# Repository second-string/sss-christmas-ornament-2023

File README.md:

# Berghain PCB Christmas Ornament
Designed by Second String Studios

## Boards

## Layout

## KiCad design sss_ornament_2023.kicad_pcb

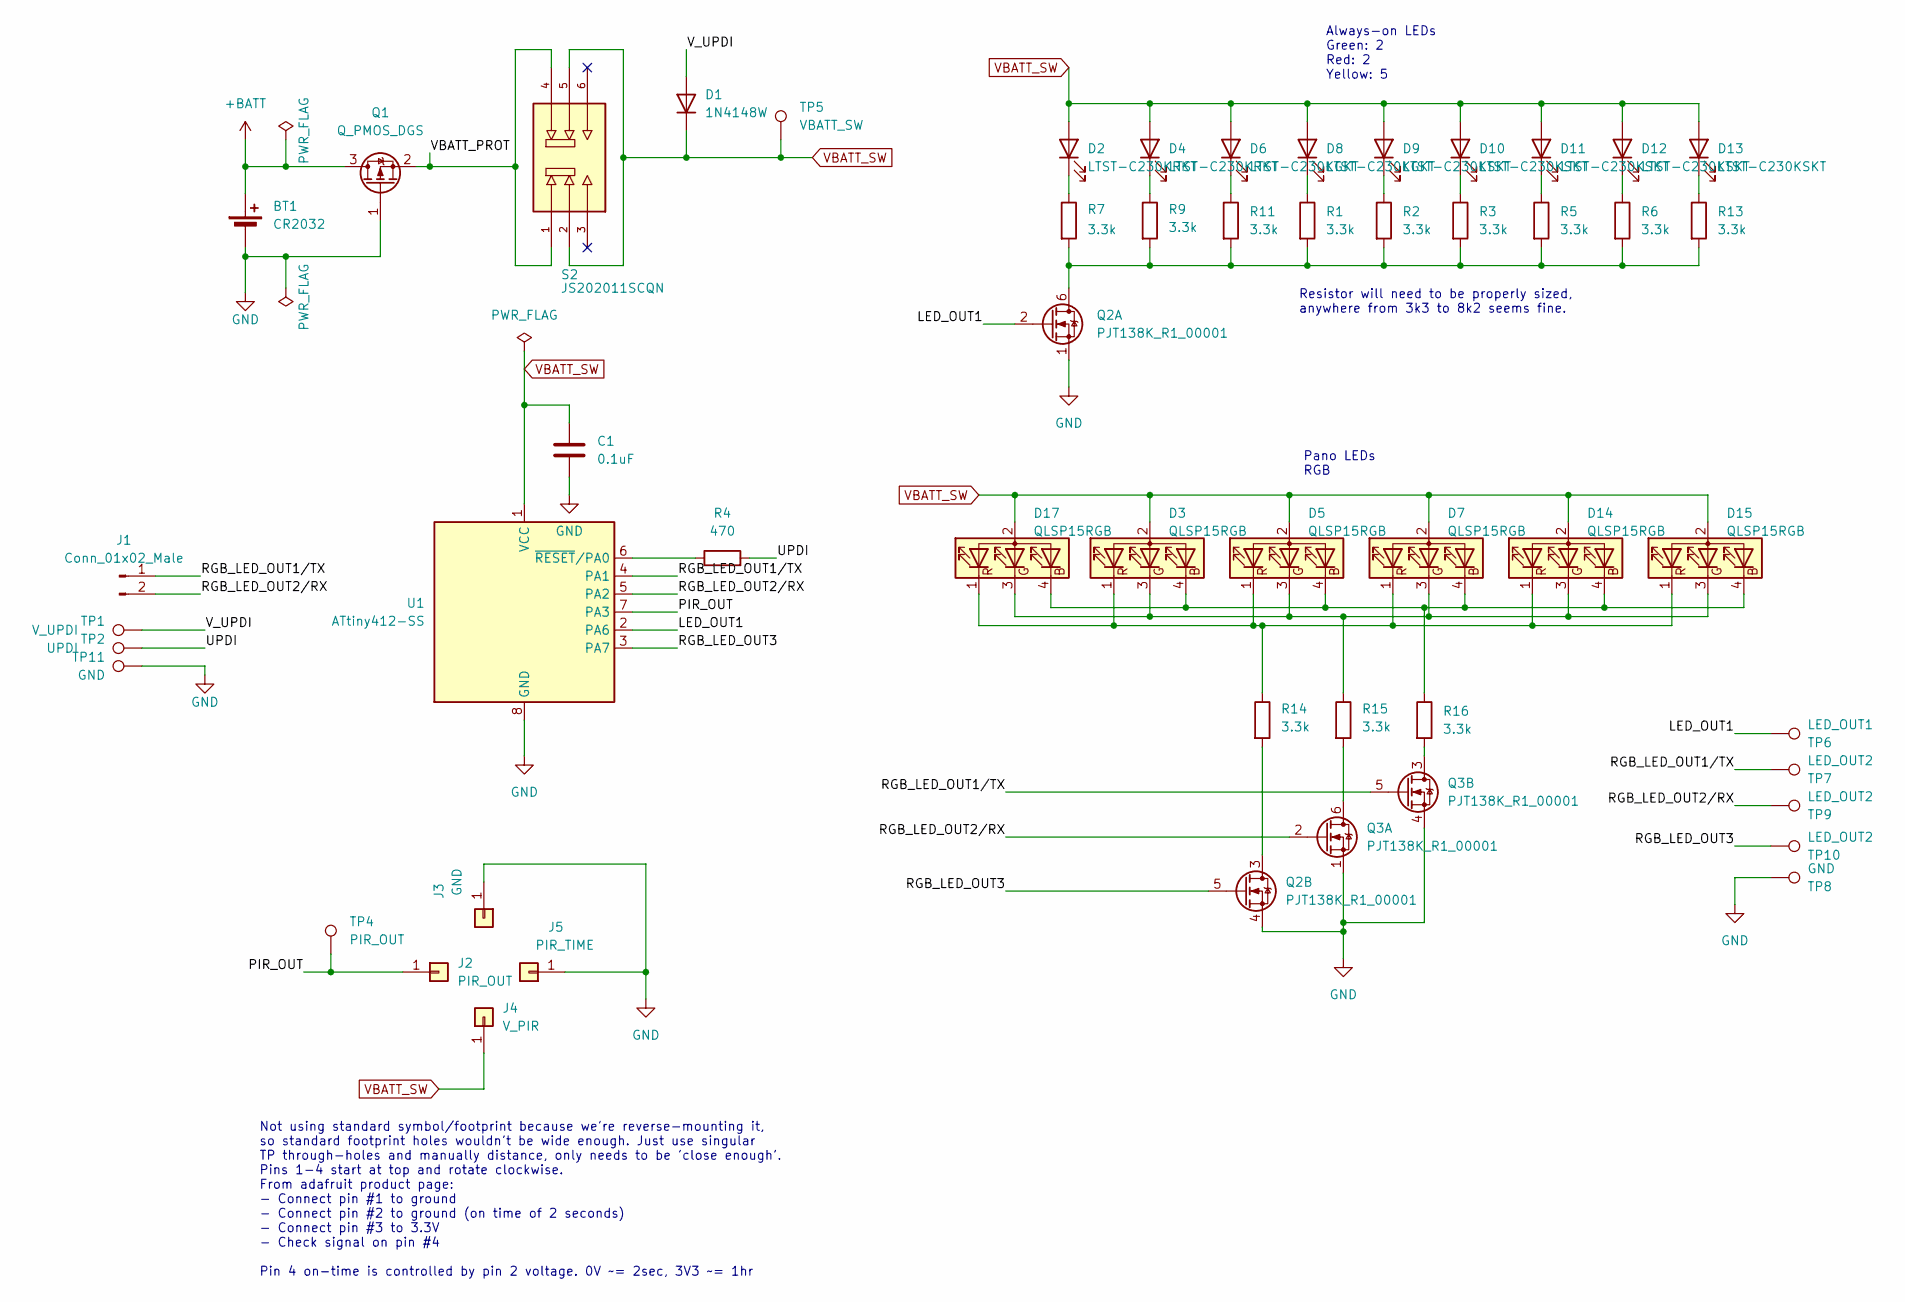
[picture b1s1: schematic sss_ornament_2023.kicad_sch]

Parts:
BT1: CR2032; BatteryHolder_Keystone_3002_1x2032
C1: 0.1uF; C_0805_2012Metric_Pad1.18x1.45mm_HandSolder
D1: 1N4148W; D_SOD-123
D2, D4: LTST-C230KRKT; LED_LTST-C230K
D3, D5, D7, D14, D15, D17: QLSP15RGB
D6, D8: LTST-C230KGKT; LED_LTST-C230K
D9, D10, D11, D12, D13: LTST-C230KSKT; LED_LTST-C230K
J1: Conn_01x02_Male; Harwin_M20-89003xx_1x02_P2.54mm_Horizontal
J2: PIR_OUT; PinHeader_1x01_P2.54mm_Vertical
J3: GND; PinHeader_1x01_P2.54mm_Vertical
J4: V_PIR; PinHeader_1x01_P2.54mm_Vertical
J5: PIR_TIME; PinHeader_1x01_P2.54mm_Vertical
Q1: Q_PMOS_DGS; SOT-723
Q2, Q3: PJT138K_R1_00001; SOT-363_SC-70-6_Handsoldering
R1, R2, R3, R5, R6, R7, R9, R11, R13, R14, R15, R16: 3.3k; R_0805_2012Metric_Pad1.20x1.40mm_HandSolder
R4: 470; R_0805_2012Metric_Pad1.20x1.40mm_HandSolder
S2: JS202011SCQN; SW_JS202011SCQN
TP1: V_UPDI; TestPoint_Pad_D2.0mm
TP2: UPDI; TestPoint_Pad_D2.0mm
TP4: PIR_OUT; TestPoint_Pad_D2.0mm
TP5: VBATT_SW; TestPoint_Pad_D2.0mm
TP6: LED_OUT1; TestPoint_Pad_D2.0mm
TP7, TP9, TP10: LED_OUT2; TestPoint_Pad_D2.0mm
TP8, TP11: GND; TestPoint_Pad_D2.0mm
U1: ATtiny412-SS; SOIC-8_3.9x4.9mm_P1.27mm

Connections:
+BATT: BT1.1 (+), Q1.3 (D)
/LED_OUT1: Q2.2 (G), TP6.1, U1.2 (PA6)
/PIR_OUT: J2.1, TP4.1, U1.7 (PA3)
/RGB_LED_OUT1/TX: J1.1, Q3.5 (G), TP7.1, U1.4 (PA1)
/RGB_LED_OUT2/RX: J1.2, Q3.2 (G), TP9.1, U1.5 (PA2)
/RGB_LED_OUT3: Q2.5 (G), TP10.1, U1.3 (PA7)
/UPDI: R4.2, TP2.1
/VBATT_PROT: Q1.2 (S), S2.1, S2.4
/V_UPDI: D1.2 (A), TP1.1
GND: BT1.2 (-), C1.2, J3.1, J5.1, Q1.1 (G), Q2.1 (S), Q2.4 (S), Q3.1 (S), Q3.4 (S), TP8.1, TP11.1, U1.8 (GND)
unnamed: D2.1 (K), R7.1
unnamed: D4.1 (K), R9.1
unnamed: D6.1 (K), R11.1
unnamed: D8.1 (K), R1.1
unnamed: D9.1 (K), R2.1
unnamed: D10.1 (K), R3.1
unnamed: D11.1 (K), R5.1
unnamed: D12.1 (K), R6.1
unnamed: D13.1 (K), R13.1
unnamed: D3.4 (BK), D5.4 (BK), D7.4 (BK), D14.4 (BK), D15.4 (BK), D17.4 (BK), R16.1
unnamed: D3.3 (GK), D5.3 (GK), D7.3 (GK), D14.3 (GK), D15.3 (GK), D17.3 (GK), R15.1
unnamed: D3.1 (RK), D5.1 (RK), D7.1 (RK), D14.1 (RK), D15.1 (RK), D17.1 (RK), R14.1
unnamed: Q2.6 (D), R1.2, R2.2, R3.2, R5.2, R6.2, R7.2, R9.2, R11.2, R13.2
unnamed: Q2.3 (D), R14.2
unnamed: Q3.6 (D), R15.2
unnamed: Q3.3 (D), R16.2
unnamed: R4.1, U1.6 (~RESET/PA0)
VBATT_SW: C1.1, D1.1 (K), D2.2 (A), D3.2 (A), D4.2 (A), D5.2 (A), D6.2 (A), D7.2 (A), D8.2 (A), D9.2 (A), D10.2 (A), D11.2 (A), D12.2 (A), D13.2 (A), D14.2 (A), D15.2 (A), D17.2 (A), J4.1, S2.2, S2.5, TP5.1, U1.1 (VCC)

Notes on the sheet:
Resistor will need to be properly sized, anywhere from 3k3 to 8k2 seems fine.
Pano LEDs RGB
Not using standard symbol/footprint because we're reverse-mounting it, so standard footprint holes wouldn't be wide enough. Just use singular TP through-holes and manually distance, only needs to be 'close enough'. Pins 1-4 start at top and rotate clockwise. From adafruit product page: - Connect pi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
Always-on LEDs Green: 2 Red: 2 Yellow: 5

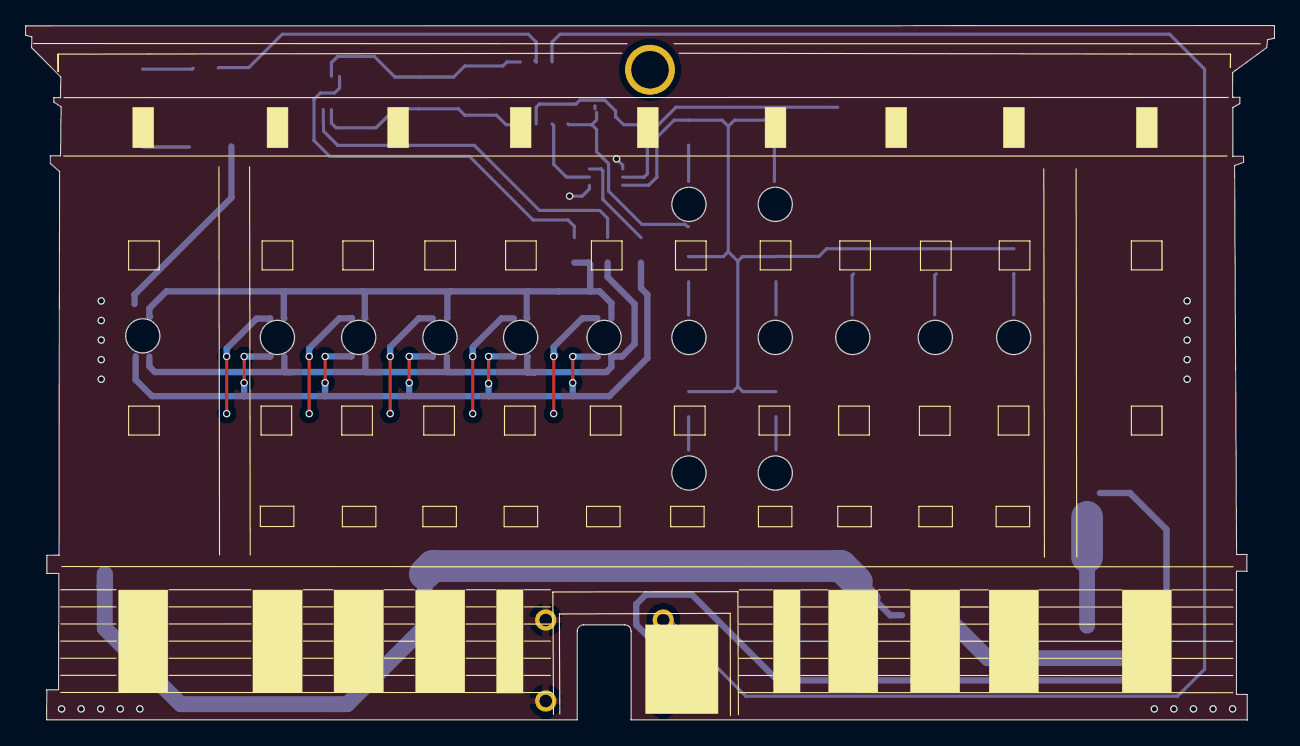
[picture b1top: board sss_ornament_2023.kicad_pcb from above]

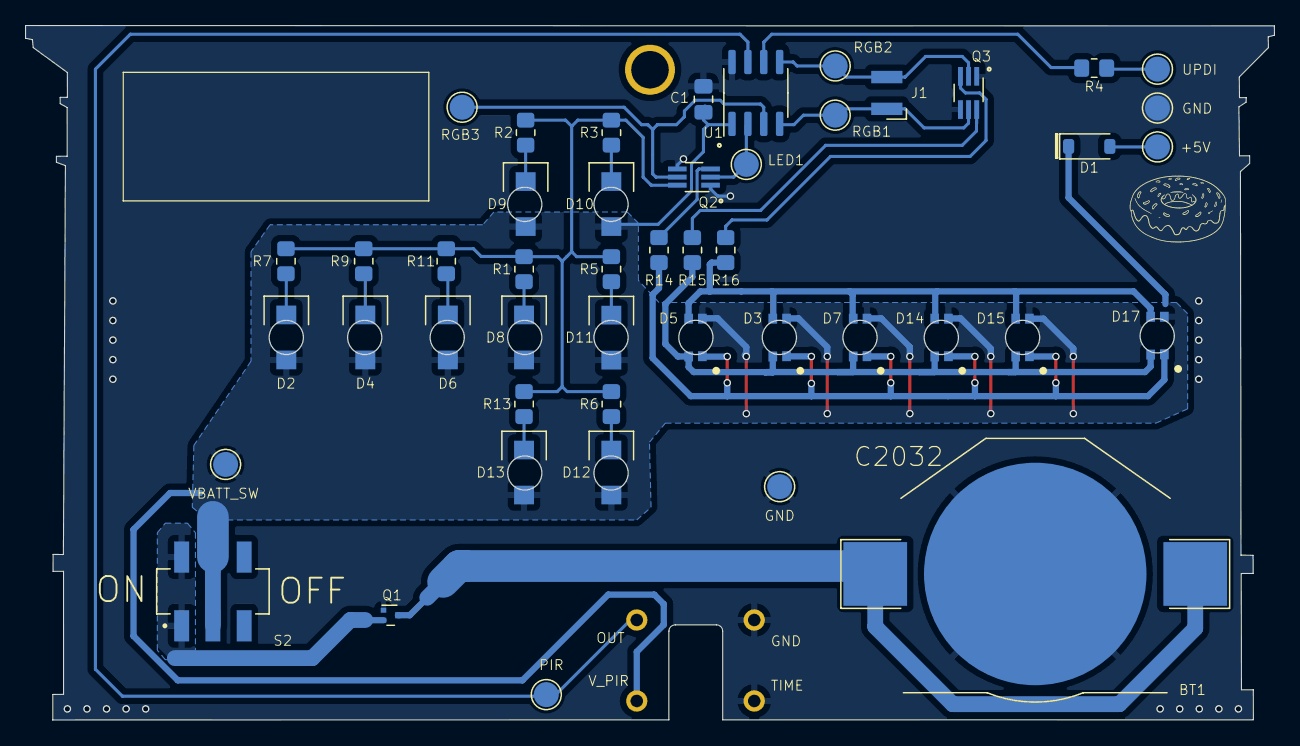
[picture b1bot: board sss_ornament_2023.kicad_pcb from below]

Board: 2 copper layers, 99.9 x 55.5 mm, 51 parts (51 on the bottom side), 28 nets.

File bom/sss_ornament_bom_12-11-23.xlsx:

Reference | Value | Menge | Footprint | Supplier URL
BT1 | CR2032 | 1 | Battery:BatteryHolder_Keystone_3002_1x2032 | https://www.digikey.de/en/products/detail/adam-tech/BH-67D-5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
C1 | 0.1uF | 1 | Capacitor_SMD:C_0805_2012Metric_Pad1.18x1.45mm_HandSolder | https://www.digikey.de/en/products/detail/samsung-electro-me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
D1 | 1N4148W | 1 | Diode_SMD:D_SOD-123 | https://www.digikey.de/en/products/detail/smc-diode-solution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
D2, D4 | LTST-C230KRKT | 2 | LTST-C230K:LED_LTST-C230K | https://www.digikey.de/en/products/detail/liteon/LTST-C230KR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
D3, D5, D7, D14, D15, D17 | QLSP15RGB | 6 | QLSP15RGB:QLSP15RGB | https://www.digikey.de/en/products/detail/quelighting-corp/Q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
D6, D8 | LTST-C230KGKT | 2 | LTST-C230K:LED_LTST-C230K | https://www.digikey.de/en/products/detail/liteon/LTST-C230KG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
D9-D13 | LTST-C230KSKT | 5 | LTST-C230K:LED_LTST-C230K | https://www.digikey.de/en/products/detail/liteon/LTST-C230KS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
Q1 | Q_PMOS_DGS | 1 | Package_TO_SOT_SMD:SOT-723 | https://www.digikey.de/en/products/detail/toshiba-semiconduc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
Q2, Q3 | PJT138K_R1_00001 | 2 | Package_TO_SOT_SMD:SOT-363_SC-70-6_Handsoldering | https://www.digikey.de/en/products/detail/panjit-internation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
R1-R3, R5-R7, R9, R11, R13-R16 | 3.3k | 12 | Resistor_SMD:R_0805_2012Metric_Pad1.20x1.40mm_HandSolder | https://www.digikey.de/en/products/detail/yageo/RC0805FR-078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
R4 | 470 | 1 | Resistor_SMD:R_0805_2012Metric_Pad1.20x1.40mm_HandSolder | https://www.digikey.de/en/products/detail/yageo/RC0805JR-074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
U1 | ATtiny412-SS | 1 | Package_SO:SOIC-8_3.9x4.9mm_P1.27mm | https://www.digikey.de/en/products/detail/microchip-technolo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
S2 | JS202011SCQN | 1 | SW_JS202011SCQN | https://www.digikey.de/en/products/detail/c-k/JS202011SCQN/2094299
XX | 1528-4667-ND | 1 | 4 through-holes manually placed | https://www.digikey.de/en/products/detail/adafruit-industrie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

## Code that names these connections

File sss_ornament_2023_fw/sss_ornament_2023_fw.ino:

#include <avr/sleep.h>

#define PANO_LED_R_PIN PIN_PA7
#define PANO_LED_G_PIN PIN_PA2
#define PANO_LED_B_PIN PIN_PA1
#define HOUSE_LED_PIN PIN_PA6
#define PIR_IN PIN_PA3

/*
 * Calling it duty cycle but it's the 0-255 value used for analogWrite PWM
 */
#define PANO_LED_DUTY_CYCLE (70)

/*
 * Value between 0 (fully off) and 0xFFF (fully on)
 * Set for house LEDs manually by finding a balance between bright enough to look good, while dim enough to not waste a ton of power since they're always on while awake
 */
#define HOUSE_LED_CMPCLR (0x0FF)

#define SLEEP_TIMEOUT_MIN (15)
#define SLEEP_TIMEOUT_MS (1000UL * 60 * SLEEP_TIMEOUT_MIN)

#if F_CPU != 1000000
#error Must set clock to 1MHz and must burn bootloader for 1MHz operation! PWM for pano LEDs and the delay() timing is fucky with 20MHz clock when we use both TCA (analogWrite) and TCD
#endif

typedef enum {
  PANO_COLOR_RED,
  PANO_COLOR_GREEN,
  PANO_COLOR_BLUE,
  PANO_COLOR_BROWN,
  PANO_COLOR_CYAN,
  PANO_COLOR_YELLOW,

  PANO_COLOR_COUNT,
} pano_color_t;

volatile uint32_t start_ms;
pano_color_t current_pano_color;

/*
 * PIR ISR to reset timeout start_ms  
 */
ISR(PORTA_PORT_vect) {
  PORTA.INTFLAGS = 0xFF;

  // Refresh start time every time PIR triggers. millis doesn't increment in an ISR but we don't
  // care, just refresh to the most recent time. It's also fast enough and ISR safe to do here.
  start_ms = millis();
}

/*
 * Write specified 0-255 duty cycle to correct RGB pins depending on color
 */
void pano_led_write(pano_color_t color, uint8_t duty_cycle) {
    switch (color) {
      case PANO_COLOR_RED:
        analogWrite(PANO_LED_R_PIN, duty_cycle);
        digitalWrite(PANO_LED_G_PIN, LOW);
        digitalWrite(PANO_LED_B_PIN, LOW);
        break;
      case PANO_COLOR_GREEN:
        analogWrite(PANO_LED_G_PIN, duty_cycle);
        digitalWrite(PANO_LED_R_PIN, LOW);
        digitalWrite(PANO_LED_B_PIN, LOW);
        break;
      case PANO_COLOR_BLUE:
        analogWrite(PANO_LED_B_PIN, duty_cycle);
        digitalWrite(PANO_LED_R_PIN, LOW);
        digitalWrite(PANO_LED_G_PIN, LOW);
        break;
      case PANO_COLOR_BROWN:
        analogWrite(PANO_LED_R_PIN, duty_cycle);
        analogWrite(PANO_LED_G_PIN, duty_cycle);
        digitalWrite(PANO_LED_B_PIN, LOW);
        break;
      case PANO_COLOR_CYAN:
        analogWrite(PANO_LED_G_PIN, duty_cycle);
        analogWrite(PANO_LED_B_PIN, duty_cycle);
        digitalWrite(PANO_LED_R_PIN, LOW);
        break;
      case PANO_COLOR_YELLOW:
        analogWrite(PANO_LED_R_PIN, duty_cycle);
        analogWrite(PANO_LED_B_PIN, duty_cycle);
        digitalWrite(PANO_LED_G_PIN, LOW);
        break;
       default:
        digitalWrite(PANO_LED_R_PIN, LOW);
        digitalWrite(PANO_LED_G_PIN, LOW);
        digitalWrite(PANO_LED_B_PIN, LOW);
    }
}

/*
 * Fade in / out in specified timeframes
 */
void pano_led_pulse(pano_color_t color, uint32_t on_duration_ms, uint32_t off_duration_ms) {
  int step_delay_ms = 10;
  
  int steps = on_duration_ms / step_delay_ms;
  int duty_increment = PANO_LED_DUTY_CYCLE / steps;
  for (int new_duty = 0; new_duty <= PANO_LED_DUTY_CYCLE; new_duty += duty_increment) {
    pano_led_write(color, new_duty);
    delay(step_delay_ms);
  }

  steps = off_duration_ms / step_delay_ms;
  duty_increment = PANO_LED_DUTY_CYCLE / steps;
  for (int new_duty = PANO_LED_DUTY_CYCLE; new_duty >= 0; new_duty -= duty_increment) {
    pano_led_write(color, new_duty);
    delay(step_delay_ms);
  }
}

void deep_sleep() {
  // Turn off all LEDs before sleeping
  digitalWrite(PANO_LED_R_PIN, LOW);
  digitalWrite(PANO_LED_G_PIN, LOW);
  digitalWrite(PANO_LED_B_PIN, LOW);
  digitalWrite(HOUSE_LED_PIN, LOW);
  
  sleep_enable();
  set_sleep_mode(SLEEP_MODE_STANDBY);
  sleep_cpu();

  // Disable once (if) we wake back up and refresh sleep timer
  start_ms = millis();
  sleep_disable();
}

void house_led_pwm_init(void) {
    // Enable-protected reg must have 0 written to enable bit before any other bits can be changed, and it defaults to
    // enabled on startup
    TCD0.CTRLA &= ~TCD_ENABLE_bm;

    // Don't need overlapping PWM signals so just do oneramp
    TCD0.CTRLB = TCD_WGMODE_ONERAMP_gc;

    // Disable all input control
    TCD0.INPUTCTRLA = TCD_INPUTMODE_NONE_gc;

    // Set/clear values to create desired duty cycle. Don't care about CMPB (outputs on PA7) at all so leave it off
    TCD0.CMPASET = 0x000;
    TCD0.CMPACLR = HOUSE_LED_CMPCLR;
    
    // System 1MHz clock w/ DIV4 standard prescaler but no synchronization prescaler (I think they multiply together, not add).
    // Must be done as last operation before starting timer with ENABLE bit
    // NOTE :: DEFAULT TIMER FOR MILLIS/MICROS FUNCTIONS ON 1-SERIES ATTINIES IS TCD. I think this still works with it set as the default,
    // but if not, try switching it to TCB0.
    TCD0.CTRLA = TCD_CLKSEL_SYSCLK_gc | TCD_CNTPRES_DIV4_gc | TCD_SYNCPRES_DIV1_gc;
}

void house_led_pwm_start(void) {
  // Turn off output override (because we want pwm to run it duh)
  TCD0.CTRLC &= ~TCD_CMPOVR_bm;
    
  // Enable WOA (PA6) but not and WOB/C/D (PA7/?/?). Since FAULTCTRL reg is write protected we need to make it editable in
  // CCP reg. Must be done in start func because we can't take over output pins in stop func unless we disable them in FAULTCTRL.
  CPU_CCP        = CCP_IOREG_gc;
  TCD0.FAULTCTRL = TCD_CMPAEN_bm;
  
  while (!(TCD0.STATUS & TCD_ENRDY_bm)) {
      ;
  }

  TCD0.CTRLA |= TCD_ENABLE_bm;
}

/*
 * Must be called every time TCD0.CMPASET or TCD0.CMPACLR are updated for them to take effect if they're changed while PWM running.
 */
void house_led_pwm_sync(void) {
    TCD0.CTRLE = TCD_SYNCEOC_bm;
}


void setup() {
  pinMode(PANO_LED_R_PIN, OUTPUT);
  pinMode(PANO_LED_G_PIN, OUTPUT);
  pinMode(PANO_LED_B_PIN, OUTPUT);
  pinMode(HOUSE_LED_PIN, OUTPUT);

  house_led_pwm_init();
  house_led_pwm_start();

  current_pano_color = PANO_COLOR_RED;

  // Set up interrupt on PIR pin. Must be BOTHEDGES or LEVEL since we're using a partially-async pin. If using PA2
  // or PA6 (fully async), can wake from deep sleep with any trigger.
  PORTA.PIN3CTRL = (PORTA.PIN3CTRL & ~PORT_ISC_gm) | PORT_ISC_BOTHEDGES_gc | PORT_PULLUPEN_bm;
  
  sei();
}

void loop() {
//   If we've reached timeout with nothing, that means either no movement or constant movement for the timeout period.
//   If the PIR pin is still high, that means it's continuously reported movement, so just refresh the timeout time. If
//   it's low, then the timeout has actually elapsed with no trigger, so sleep.
  if ((millis() - start_ms) > SLEEP_TIMEOUT_MS) {
    if (digitalRead(PIR_IN) == LOW) {
      deep_sleep();
    } else {
      start_ms = millis();
    }
  }

// 150BPM I think...
  pano_led_pulse(current_pano_color, 200, 200);
  pano_led_pulse(current_pano_color, 200, 200);
  pano_led_pulse(current_pano_color, 200, 200);

  pano_led_pulse(current_pano_color, 100, 100);
  pano_led_pulse(current_pano_color, 100, 100);

  current_pano_color = (pano_color_t)((uint8_t)current_pano_color + 1);
  if (current_pano_color == PANO_COLOR_COUNT) {
    current_pano_color = PANO_COLOR_RED;
  }
}

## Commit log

2023-11-11 Initial commit of 2023 project skeleton kicad project. Schematic has previous year's design imported with no changes as base to build upon similar motion-activated-LED design.
2024-01-14 Completed 2023 ornament kicad project and all necessary bom/gerber/datasheet/document data
2024-01-14 Completed 2023 ornament firmware for attiny412 flashed over UPDI using megaTinyCore through arduino framework
2024-02-24 add kicad lock files to gitignore
2024-02-24 Add design images and add to readme
2024-03-02 gitignore media folder
